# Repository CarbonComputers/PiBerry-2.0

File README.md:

# PiBerry- 1.7 - 2.0
PiBerry 1.7 - 2.0 build guide and relevant files

The PiBerry 1.8 is a compact, modular cyberdeck built for Raspberry Pi Zero 2W, designed with DIY in mind. Perfect for tech enthusiasts, it combines a traditional 3.5" touchscreen, a Blackberry-style keyboard from Zitao Tech, and flexible power solutions by PiSugar for on-the-go hacking and DIY projects.

Easy to build
Solder the display to the PCB, and Solder or mount the Pi to the back of the PCB
Wire the USB Zitao blackberry keyboard with a small cable or flat FPC flexible cable to the Pi Zero USB port (Alternatively you can use the BT version of the BBQ20 by Zitao) (https://www.tindie.com/products/zitaotech/blackberry-bb9900-usb-keyboard-with-trackpad/)
To power the unit you can use the PiSugar 1,200 mAh (https://a.co/d/7HnG4I7)

Lastly, print or order the 3D-printed case

Key Features
Touchscreen Compatibility with popular 3.5" displays
Compact Design with modular upgrade options
For purchase, visit CarbonComputers.us

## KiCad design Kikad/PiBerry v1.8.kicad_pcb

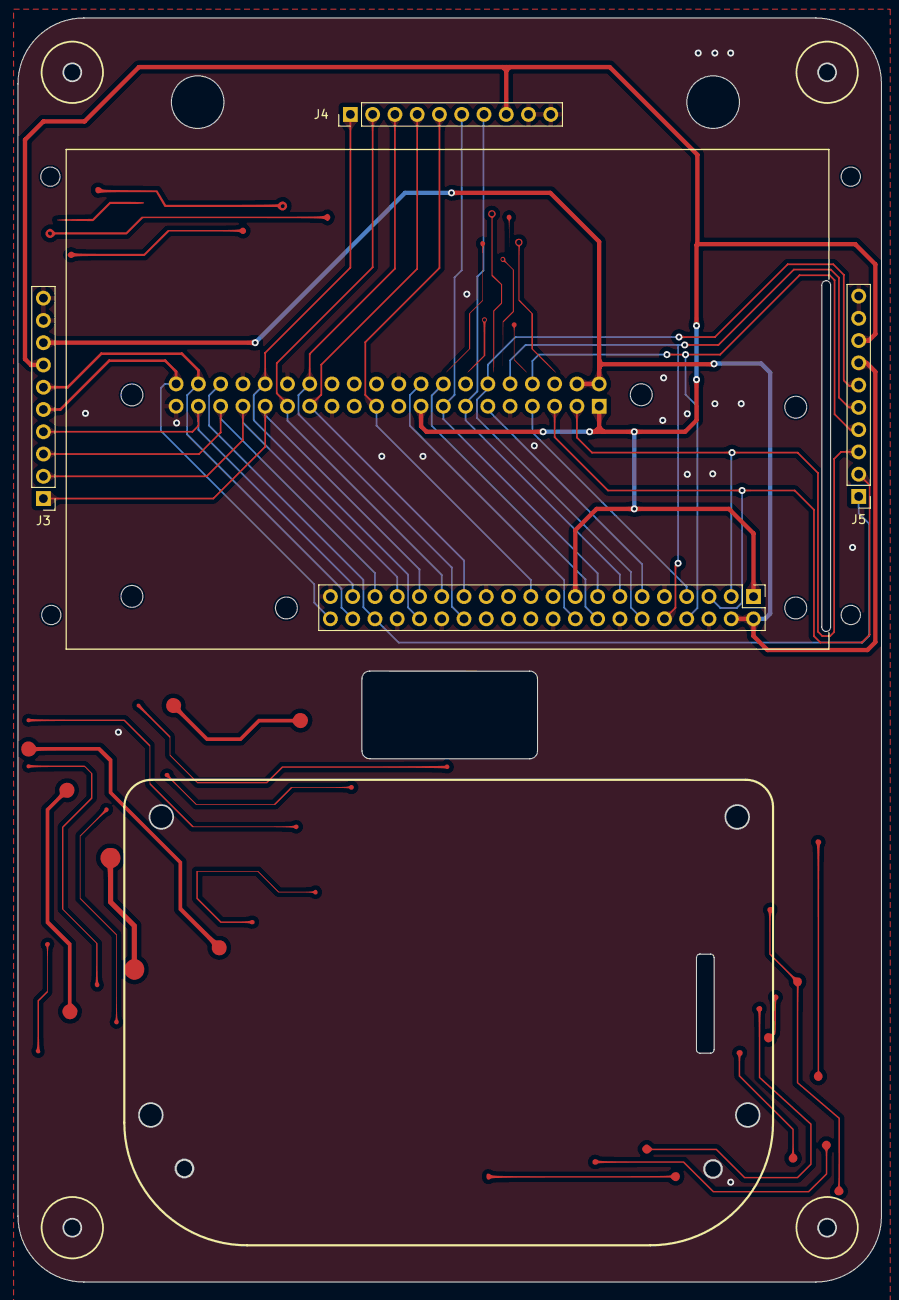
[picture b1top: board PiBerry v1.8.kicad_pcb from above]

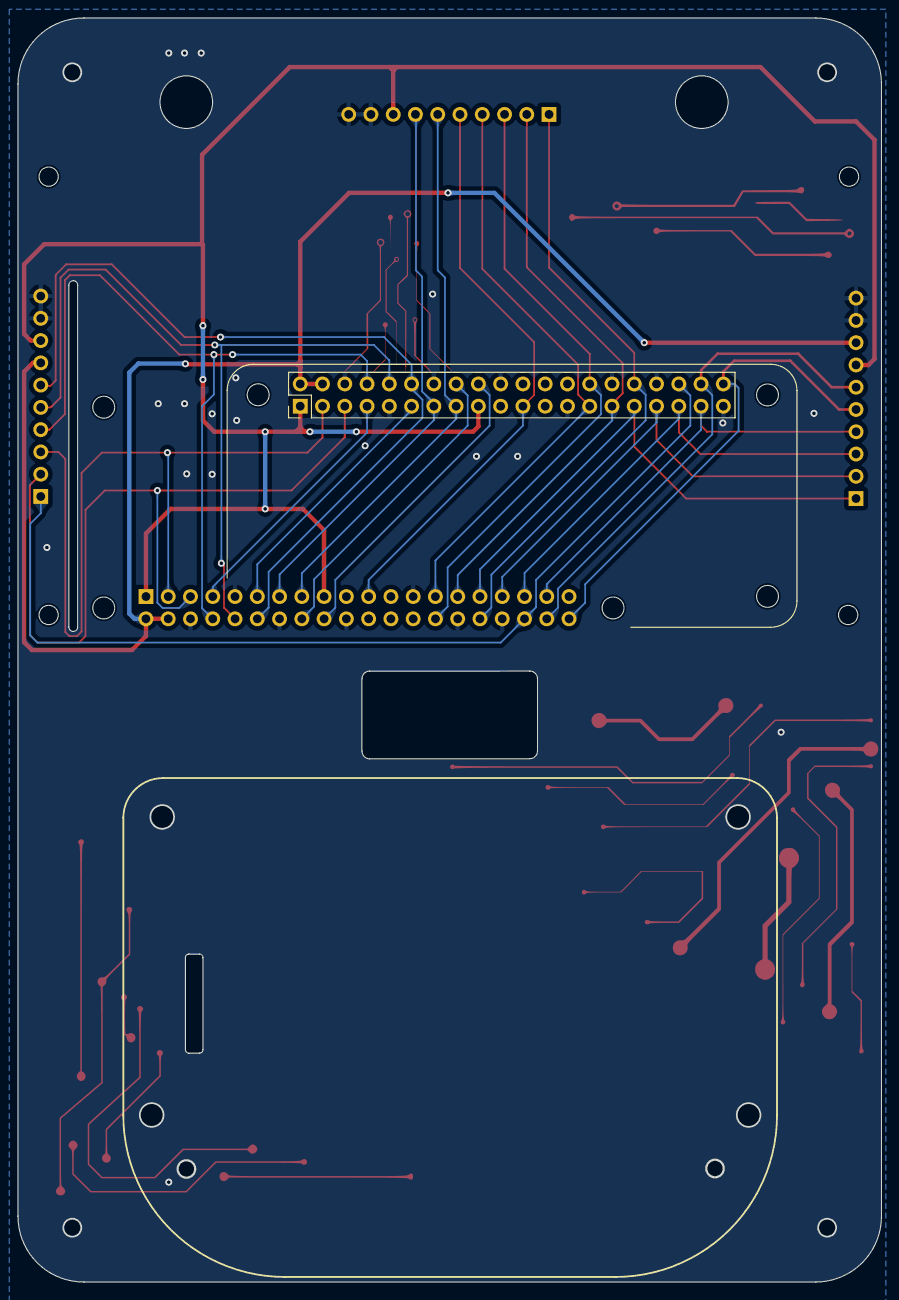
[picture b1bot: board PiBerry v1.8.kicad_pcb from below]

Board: 2 copper layers, 98.5 x 144.2 mm, 15 parts (4 on the bottom side), 26 nets.

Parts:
H1, H4, H7, H10: MountingHole; MountingHole_2.2mm_M2
H2, H3, H5, H6, H8, H11: MountingHole; MountingHole_2.5mm
J1, J2: RPi_GPIO; PinHeader_2x20_P2.54mm_Vertical
J3: Header 1; PinHeader_1x10_P2.54mm_Vertical
J4: Header 2; PinHeader_1x10_P2.54mm_Vertical
J5: Header 3; PinHeader_1x10_P2.54mm_Vertical

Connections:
+3.3V: J1.1 (3.3V), J1.17 (3.3V), J2.1 (3.3V), J2.17 (3.3V), J3.7, J4.8, J5.8
+5V: J1.2 (5V), J1.4 (5V), J2.2 (5V), J2.4 (5V), J3.8, J5.7
/Button: J1.11 (GPIO17), J2.11 (GPIO17)
/DISP_EXTIN: J1.16 (GPIO23), J2.16 (GPIO23)
/PI_HEADER_SWDIO: J1.18 (GPIO24), J2.18 (GPIO24)
/Pi_GPIO0: J1.27 (ID_SD), J2.27 (ID_SD), J4.4
/Pi_GPIO1: J1.28 (ID_SC), J2.28 (ID_SC), J4.3
/Pi_GPIO5: J1.29 (GPIO05), J2.29 (GPIO05), J4.2
/Pi_GPIO6: J1.31 (GPIO06), J2.31 (GPIO06), J3.1
/Pi_GPIO09: J1.21 (GPIO09_SPI_MISO), J2.21 (GPIO09_SPI_MISO), J4.5
/Pi_GPIO12: J1.32 (GPIO12), J2.32 (GPIO12), J4.1
/Pi_GPIO13: J1.33 (GPIO13), J2.33 (GPIO13), J3.2
/Pi_GPIO14: J1.8 (GPIO14_TXD0), J2.8 (GPIO14_TXD0), J5.4
/Pi_GPIO15: J1.10 (GPIO15_RXD0), J2.10 (GPIO15_RXD0), J5.5
/Pi_GPIO16: J1.36 (GPIO16), J2.36 (GPIO16), J5.1
/Pi_GPIO18: J1.12 (GPIO18), J2.12 (GPIO18), J5.6
/Pi_GPIO19: J1.35 (GPIO19), J2.35 (GPIO19), J3.3
/Pi_GPIO20: J1.38 (GPIO20), J2.38 (GPIO20), J3.6
/Pi_GPIO21: J1.40 (GPIO21), J2.40 (GPIO21), J3.5
/Pi_GPIO22: J1.15 (GPIO22), J2.15 (GPIO22), J4.6
/Pi_GPIO26: J1.37 (GPIO26), J2.37 (GPIO26), J3.4
/Pi_GPIO27: J1.13 (GPIO27), J2.13 (GPIO27), J4.7
/Pi_INT: J1.7 (GPIO04_GCLK), J2.7 (GPIO04_GCLK)
/Pi_SCL: J1.5 (GPIO03_SCL1_I2C), J2.5 (GPIO03_SCL1_I2C), J5.2
/Pi_SDA: J1.3 (GPIO02_SDA1_I2C), J2.3 (GPIO02_SDA1_I2C), J5.3
GND: J1.6 (GND), J1.9 (GND), J1.14 (GND), J1.20 (GND), J1.25 (GND), J1.30 (GND), J1.34 (GND), J1.39 (GND), J2.6 (GND), J2.9 (GND), J2.14 (GND), J2.20 (GND), J2.25 (GND), J2.30 (GND), J2.34 (GND), J2.39 (GND), J3.9, J3.10, J4.9, J4.10, J5.9, J5.10

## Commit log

2024-10-11 Update README.md
    minor
2024-11-02 Uploading all project files
2024-11-02 Update README.md
    inserting photos
2024-11-02 Update README.md
    photo link broken
2024-11-02 Update README.md
    minor link
2024-11-02 Update README.md
    spelling
